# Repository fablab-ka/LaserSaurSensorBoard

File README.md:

# LaserSaurSensorBoard
Sensor Board for the LaserSaur wich processes filter values, temperatures, ... and disables the Laser Tube when needed

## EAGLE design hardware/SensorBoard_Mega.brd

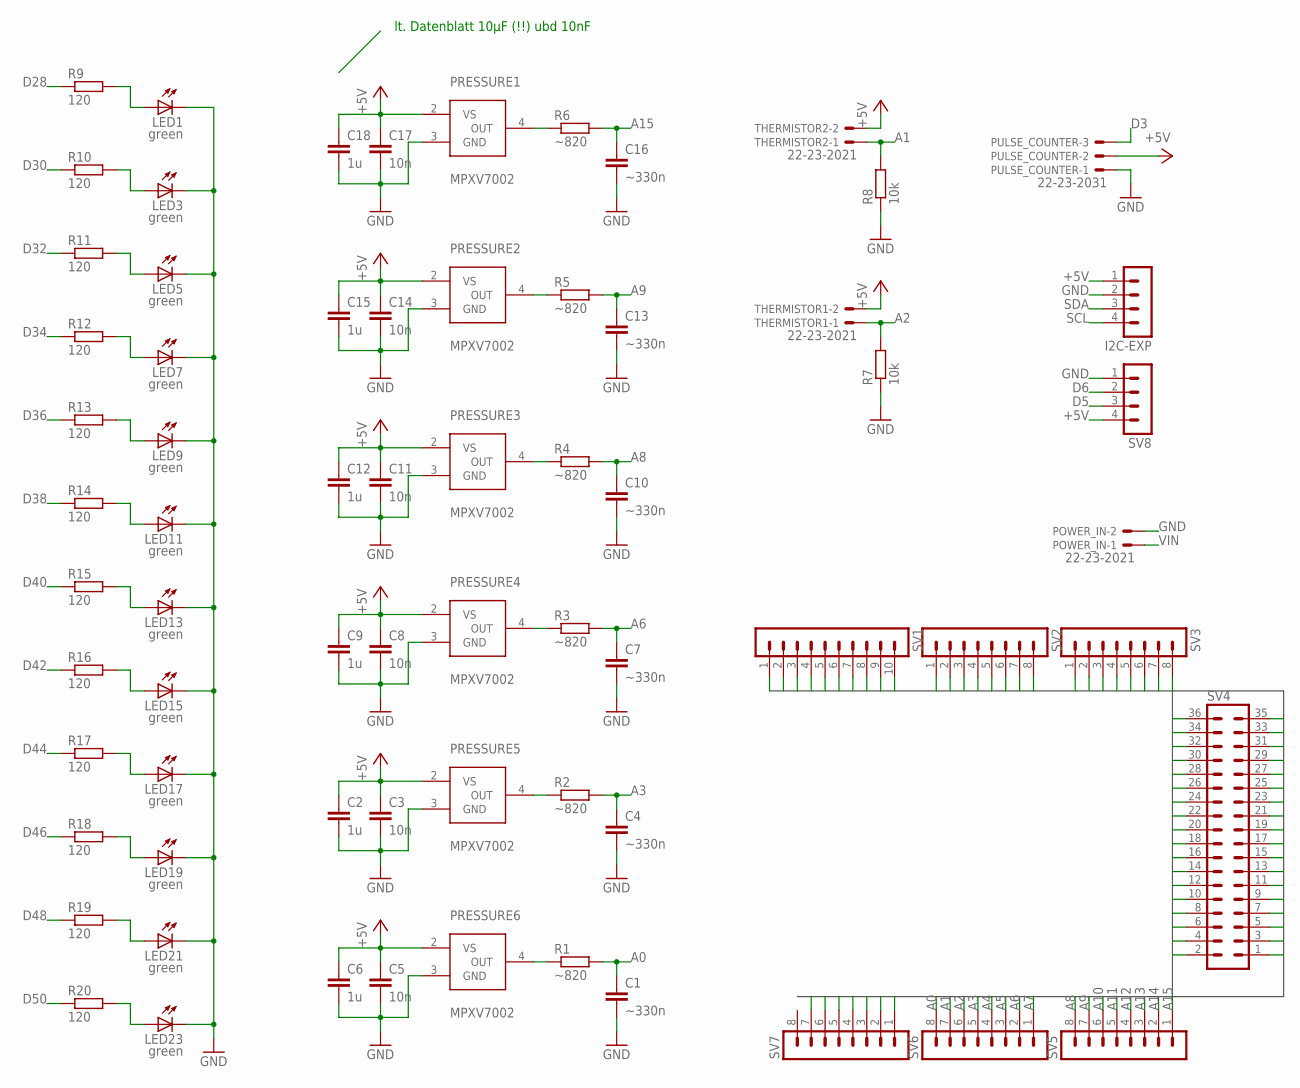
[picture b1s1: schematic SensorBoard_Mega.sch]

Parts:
C1, C4, C7, C10, C13, C16: ~330n; C0805
C2, C6, C9, C12, C15, C18: 1u; C0805
C3, C5, C8, C11, C14, C17: 10n; C0805
I2C-EXP: MA04-1
LED1, LED3, LED5, LED7, LED9, LED11, LED13, LED15, LED17, LED19, LED21, LED23: green; CHIPLED_0805
POWER_IN: 22-23-2021
PRESSURE1, PRESSURE2, PRESSURE3, PRESSURE4, PRESSURE5, PRESSURE6: MPXV7002; MPXV7002DP
PULSE_COUNTER: 22-23-2031
R1, R2, R3, R4, R5, R6: ~820; R0805
R7, R8: 10k; R0805
R9, R10, R11, R12, R13, R14, R15, R16, R17, R18, R19, R20: 120; R0805
SV1: MA10-1
SV2, SV3, SV5, SV6, SV7: MA08-1
SV4: MA18-2
SV8: MA04-1
THERMISTOR1, THERMISTOR2: 22-23-2021

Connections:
+3V3: SV7.5
+5V: C2.1, C3.1, C5.1, C6.1, C8.1, C9.1, C11.1, C12.1, C14.1, C15.1, C17.1, C18.1, I2C-EXP.1, PRESSURE1.2 (VS), PRESSURE2.2 (VS), PRESSURE3.2 (VS), PRESSURE4.2 (VS), PRESSURE5.2 (VS), PRESSURE6.2 (VS), PULSE_COUNTER.2, SV4.35, SV4.36, SV7.4, SV8.4, THERMISTOR1.2, THERMISTOR2.2
A0: C1.1, R1.2, SV6.8
A1: R8.2, SV6.7, THERMISTOR2.1
A2: R7.2, SV6.6, THERMISTOR1.1
A3: C4.1, R2.2, SV6.5
A4: SV6.4
A5: SV6.3
A6: C7.1, R3.2, SV6.2
A7: SV6.1
A8: C10.1, R4.2, SV5.8
A9: C13.1, R5.2, SV5.7
A10: SV5.6
A11: SV5.5
A12: SV5.4
A13: SV5.3
A14: SV5.2
A15: C16.1, R6.2, SV5.1
AREF: SV1.3
D0: SV2.8
D1: SV2.7
D2: SV2.6
D3: PULSE_COUNTER.3, SV2.5
D4: SV2.4
D5: SV2.3, SV8.3
D6: SV2.2, SV8.2
D7: SV2.1
D8: SV1.10
D9: SV1.9
D10: SV1.8
D11: SV1.7
D12: SV1.6
D13: SV1.5
D14: SV3.1
D15: SV3.2
D16: SV3.3
D17: SV3.4
D18: SV3.5
D19: SV3.6
D22: SV4.34
D23: SV4.33
D24: SV4.32
D25: SV4.31
D26: SV4.30
D27: SV4.29
D28: R9.1, SV4.28
D29: SV4.27
D30: R10.1, SV4.26
D31: SV4.25
D32: R11.1, SV4.24
D33: SV4.23
D34: R12.1, SV4.22
D35: SV4.21
D36: R13.1, SV4.20
D37: SV4.19
D38: R14.1, SV4.18
D39: SV4.17
D40: R15.1, SV4.16
D41: SV4.15
D42: R16.1, SV4.14
D43: SV4.13
D44: R17.1, SV4.12
D45: SV4.11
D46: R18.1, SV4.10
D47: SV4.9
D48: R19.1, SV4.8
D49: SV4.7
D50: R20.1, SV4.6
D51: SV4.5
D52: SV4.4
D53: SV4.3
GND: C1.2, C2.2, C3.2, C4.2, C5.2, C6.2, C7.2, C8.2, C9.2, C10.2, C11.2, C12.2, C13.2, C14.2, C15.2, C16.2, C17.2, C18.2, I2C-EXP.2, LED1.C, LED3.C, LED5.C, LED7.C, LED9.C, LED11.C, LED13.C, LED15.C, LED17.C, LED19.C, LED21.C, LED23.C, POWER_IN.2, PRESSURE1.3 (GND), PRESSURE2.3 (GND), PRESSURE3.3 (GND), PRESSURE4.3 (GND), PRESSURE5.3 (GND), PRESSURE6.3 (GND), PULSE_COUNTER.1, R7.1, R8.1, SV1.4, SV4.1, SV4.2, SV7.2, SV7.3, SV8.1
IOREF: SV7.7
unnamed: LED1.A, R9.2
unnamed: PRESSURE6.4 (OUT), R1.1
unnamed: PRESSURE5.4 (OUT), R2.1
unnamed: PRESSURE4.4 (OUT), R3.1
unnamed: PRESSURE3.4 (OUT), R4.1
unnamed: PRESSURE2.4 (OUT), R5.1
unnamed: PRESSURE1.4 (OUT), R6.1
unnamed: LED3.A, R10.2
unnamed: LED5.A, R11.2
unnamed: LED7.A, R12.2
unnamed: LED9.A, R13.2
unnamed: LED11.A, R14.2
unnamed: LED13.A, R15.2
unnamed: LED15.A, R16.2
unnamed: LED17.A, R17.2
unnamed: LED19.A, R18.2
unnamed: LED21.A, R19.2
unnamed: LED23.A, R20.2
RESET: SV7.6
SCL: I2C-EXP.4, SV1.2, SV3.8
SDA: I2C-EXP.3, SV1.1, SV3.7
VIN: POWER_IN.1, SV7.1

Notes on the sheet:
lt. Datenblatt 10µF (!!) ubd 10nF

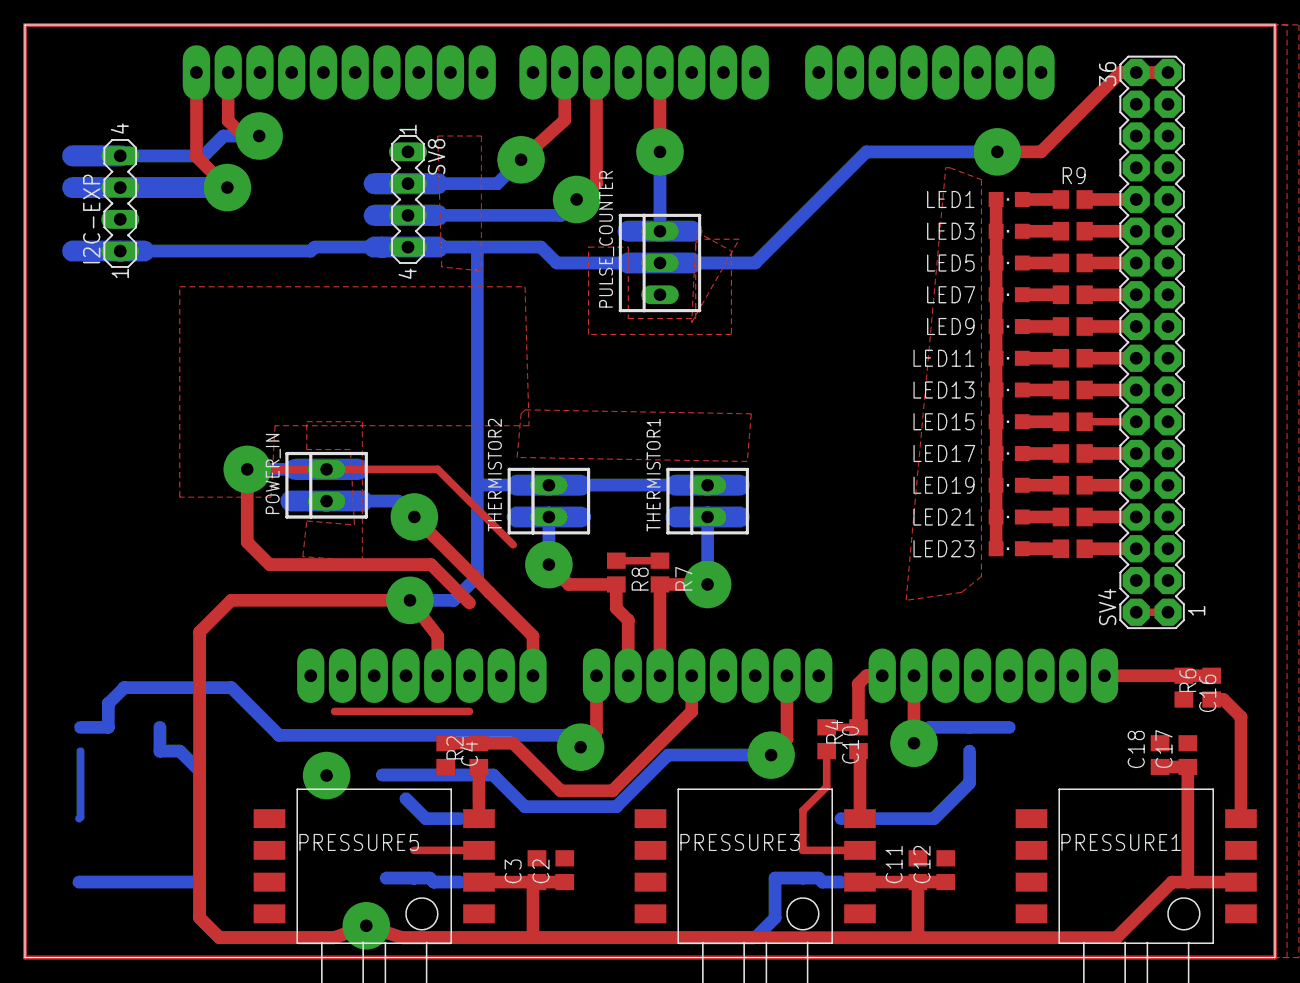
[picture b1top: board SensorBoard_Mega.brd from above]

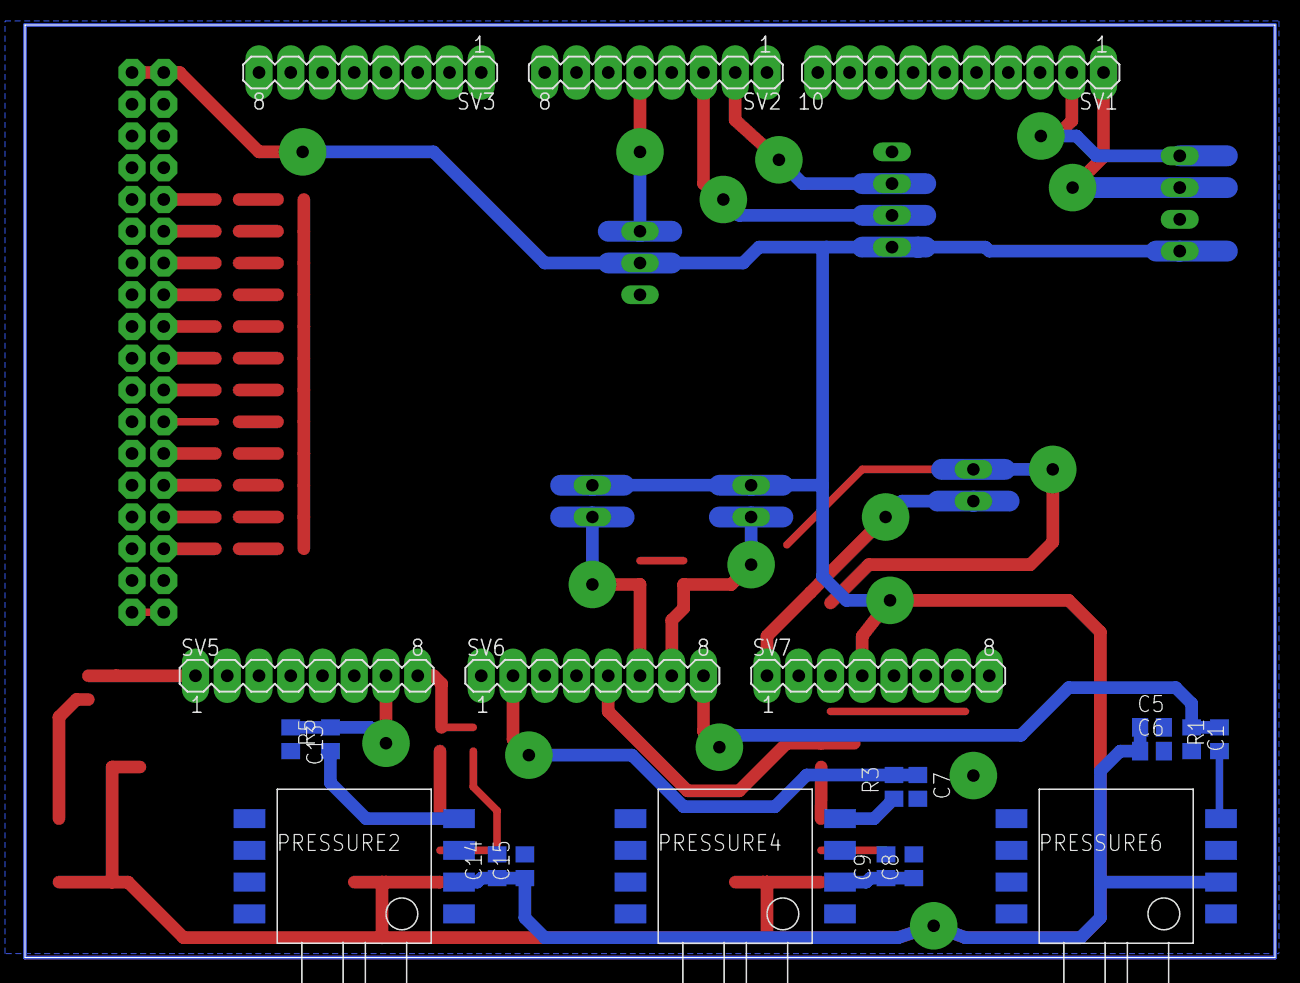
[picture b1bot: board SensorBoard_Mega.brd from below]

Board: 2 copper layers, 100.0 x 74.6 mm, 69 parts (21 on the bottom side), 46 nets.

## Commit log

2016-12-13 Initial commit
    First version of hard- and software
